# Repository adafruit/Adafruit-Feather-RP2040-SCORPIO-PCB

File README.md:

## Adafruit Feather RP2040 SCORPIO 8 Channel NeoPixel Driver PCB

<a href="http://www.adafruit.com/products/5650"><br/>
Click here to purchase one from the Adafruit shop</a>

PCB files for the Adafruit Feather RP2040 SCORPIO 8 Channel NeoPixel Driver. 

Format is EagleCAD schematic and board layout
* https://www.adafruit.com/product/5650

### Description

If there is one thing Adafruit is known for, its mega-blinky-fun-rainbow-LEDs. We just love sticking NeoPixels anywhere and everywhere. When we saw the new 'PIO' peripheral on the RP2040 from Raspberry Pi, we just knew it would be perfect for driving large quantities of NeoPixels. So we created this board, the Adafruit Feather RP2040 SCORPIO, designed specifically for NeoPixel (WS2812) driving but also good for various other PIO-based projects that want to take advantage of the Feather pinout with 8 separate consecutive outputs (or inputs).

The RP2040 PIO state machine is perfect for LED driving: it can generate perfect waveforms, with up to 8 outputs concurrently, all through DMA. That means that you don't need to use any processor time to bit-bang-out the LED data. Just set up the buffer and tell the PIO peripheral to 'make it so' and it will shove that data to the 8 outputs without delay while your code can continue to read buttons, play music, run CircuitPython - whatever you like!

The SCORPIO has a clever pinout, where all the standard Feather pins are the same as the GPIO pins, plus the standard I2C, SPI and UART lines - and theres still enough pins left over to have 8 consecutive pins for PIO usage on GPIO16 through GPIO23 inclusive.

To make NeoPixel usage glitch-free there is a 3V->5V level shifter so that the output logic is 5V. If you happen to want 3V signals, you can adjust the shifter voltage with a jumper on the bottom. It's also possible to flip the direction of the level shifter to make the 8 I/O pins inputs - say for making a logic analyzer - with a directional jumper selection also on the bottom of the PCB.

The RP2040 SCORPIO also has a ton of RAM, 264KB, making it trivial to buffer huge numbers of NeoPixels…several thousand if needed. In fact there's so much RAM you can even dither the pixels to for finer brightness control, for better-looking LEDs at low brightness or for gamma correction.

### License

Adafruit invests time and resources providing this open source design, please support Adafruit and open-source hardware by purchasing products from [Adafruit](https://www.adafruit.com)!

Designed by Limor Fried/Ladyada for Adafruit Industries.

Creative Commons Attribution/Share-Alike, all text above must be included in any redistribution. 
See license.txt for additional details.

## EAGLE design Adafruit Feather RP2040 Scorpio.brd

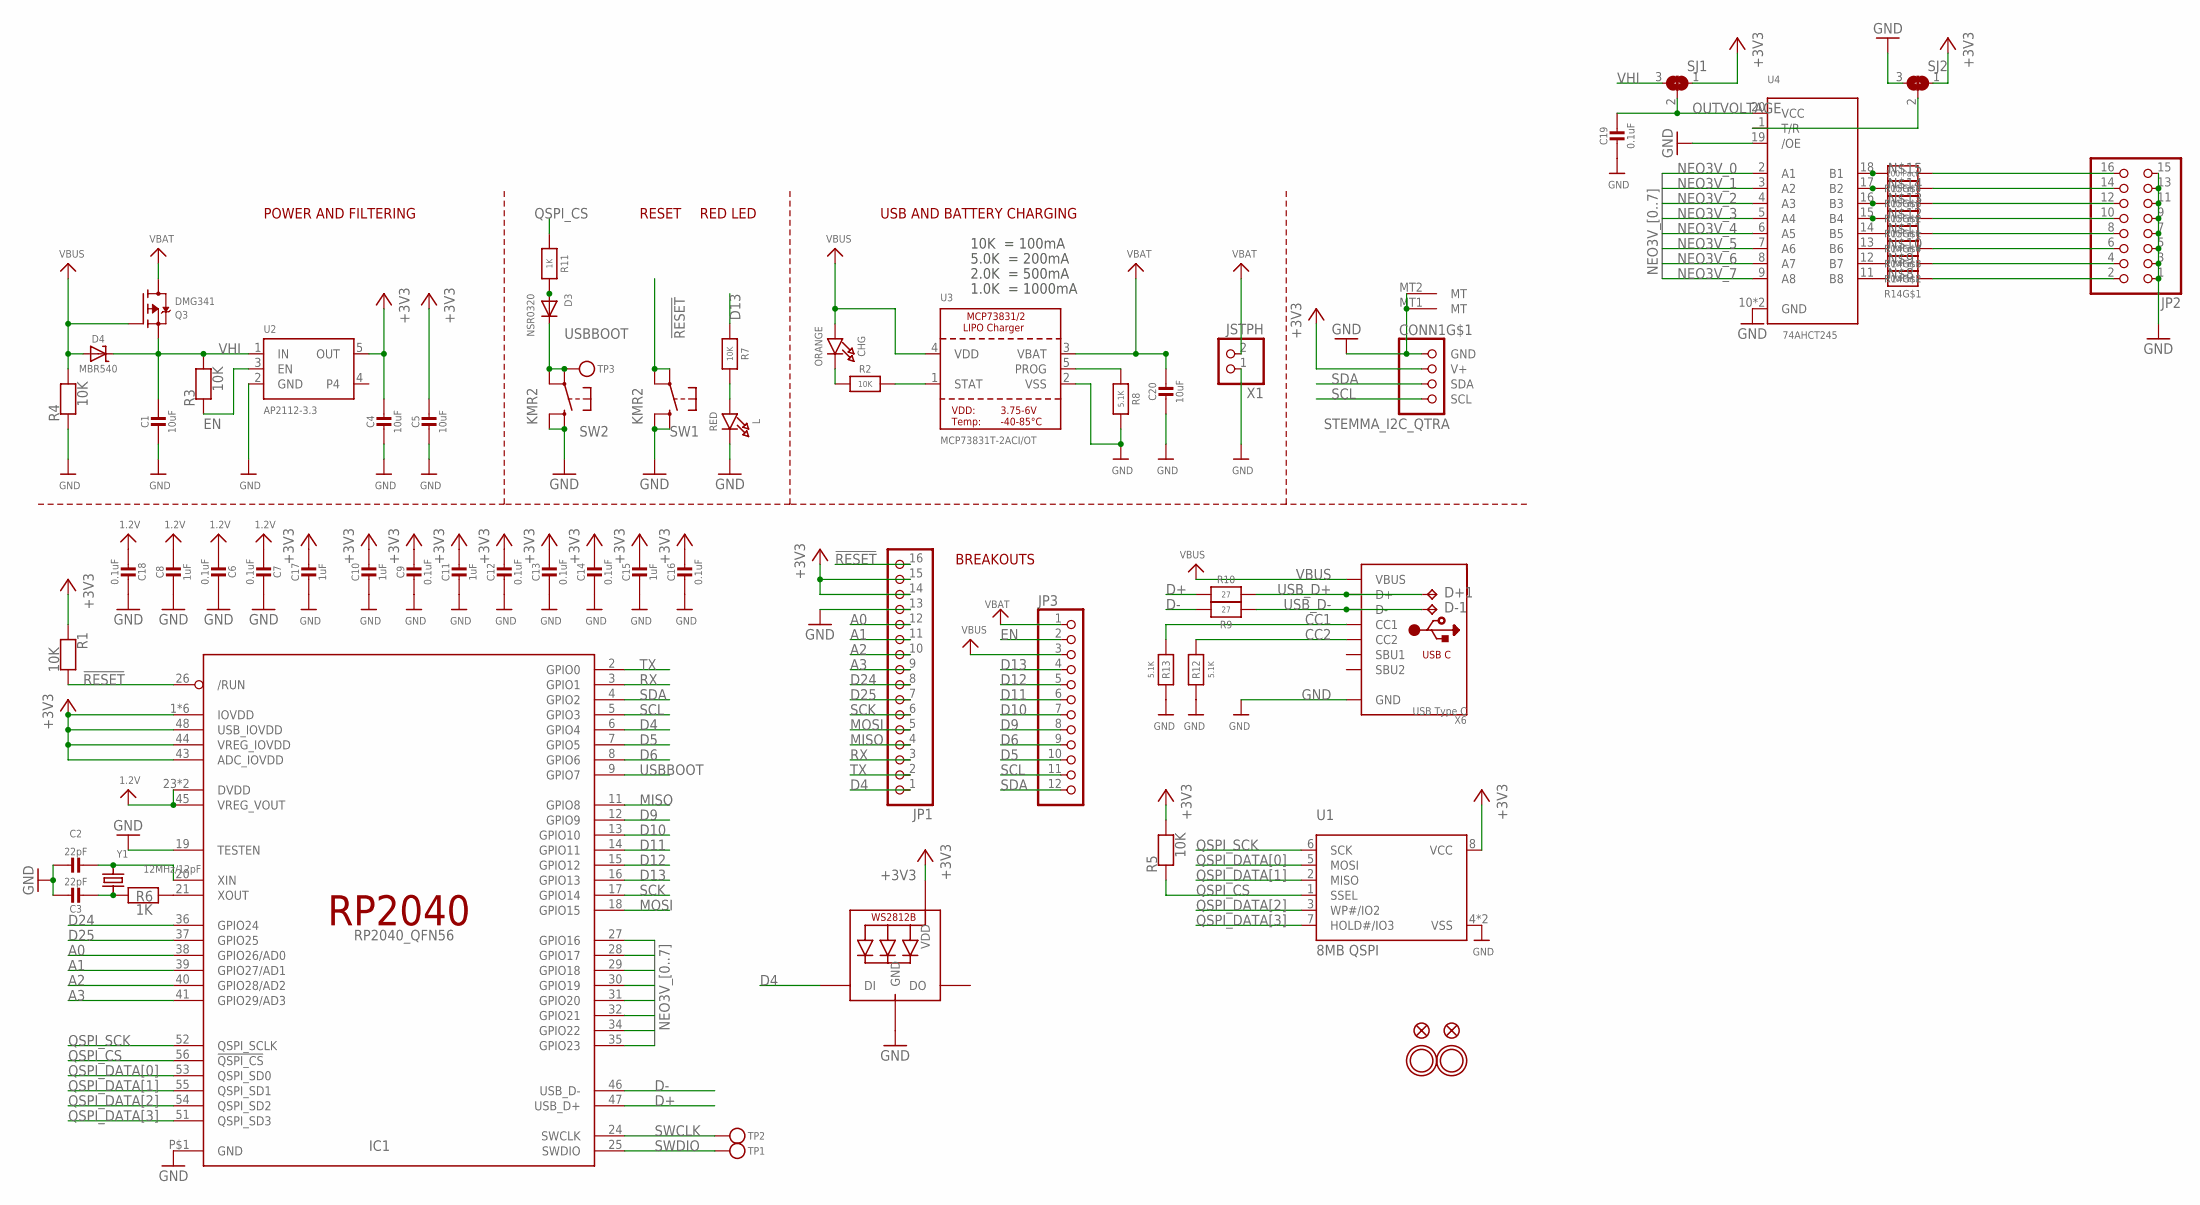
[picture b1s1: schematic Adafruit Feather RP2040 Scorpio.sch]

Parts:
C1, C4, C5, C20: 10uF; 0805-NO
C2, C3: 22pF; _0402NO
C6, C7, C9, C12, C13, C14, C16, C18, C19: 0.1uF; _0402NO
C8, C10, C11, C15, C17: 1uF; 0603-NO
CHG: ORANGE; CHIPLED_0603_NOOUTLINE
CONN1: STEMMA_I2C_QTRA; JST_SH4_RA
D3: NSR0320; SOD-323F
D4: MBR540; SOD-123
D+1: TPB1,27; B1,27
D-1: TPB1,27; B1,27
IC1: RP2040_QFN56; QFN56_7MM_REDUCEDEPAD
JP1: HEADER-1X16ROUND; 1X16_ROUND
JP2: HEADER-2X8; 2X08
JP3: HEADER-1X12; 1X12_ROUND
L: RED; CHIPLED_0603_NOOUTLINE
LED1: WS2812B_SK6805_1515; SK6805_1515
Q3: DMG341; SOT23-R
R1, R2, R3, R4, R5, R7: 10K; 0603-NO
R6, R11: 1K; 0603-NO
R8, R12, R13: 5.1K; 0603-NO
R9, R10: 27; 0603-NO
R14, R15: 100 Pack; RESPACK_4X0402
SJ1, SJ2: SOLDERJUMPER_2WAY; SOLDERJUMPER_2WAY_OPEN_NOPASTE
SW1, SW2: KMR2; BTN_KMR2_4.6X2.8
TP1, TP2, TP3: TESTPOINTROUND1.5MMNO; TESTPOINT_ROUND_1.5MM_NO
U1: 8MB QSPI; USON8_4X4
U2: AP2112-3.3; SOT23-5; JLC_ROTATION 0
U3: MCP73831T-2ACI/OT; SOT23-5
U4: 74AHCT245; 20-DHVQFN
U$31, U$32: MOUNTINGHOLE2.5; MOUNTINGHOLE_2.5_PLATED
U$34, U$35: FIDUCIAL_1MM
X1: JSTPH; JSTPH2_BATT
X6: USB Type C; USB_C_CUSB31-CFM2AX-01-X
Y1: 12MHz/12pF; CRYSTAL_2.5X2

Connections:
1.2V: C6.2, C7.2, C8.1, C18.2, IC1.23 (DVDD), IC1.45 (VREG_VOUT), IC1.50 (DVDD)
!RESET: IC1.26 (/RUN), JP1.16, R1.2, SW1.A, SW1.A' (P1)
+3V3: C4.1, C5.1, C9.1, C10.1, C11.1, C12.1, C13.1, C14.1, C15.1, C16.1, C17.1, CONN1.2 (V+), IC1.1 (IOVDD), IC1.10 (IOVDD), IC1.22 (IOVDD), IC1.33 (IOVDD), IC1.42 (IOVDD), IC1.43 (ADC_IOVDD), IC1.44 (VREG_IOVDD), IC1.48 (USB_IOVDD), IC1.49 (IOVDD), JP1.14, JP1.15, LED1.2 (VDD), R1.1, R5.2, SJ1.1, SJ2.1, U1.8 (VCC), U2.5 (OUT)
A0: IC1.38 (GPIO26/AD0), JP1.12
A1: IC1.39 (GPIO27/AD1), JP1.11
A2: IC1.40 (GPIO28/AD2), JP1.10
A3: IC1.41 (GPIO29/AD3), JP1.9
CC1: R13.2, X6.A5 (CC1)
CC2: R12.2, X6.B5 (CC2)
D4: IC1.6 (GPIO4), JP1.1, LED1.1 (DI)
D5: IC1.7 (GPIO5), JP3.10
D6: IC1.8 (GPIO6), JP3.9
D9: IC1.12 (GPIO9), JP3.8
D10: IC1.13 (GPIO10), JP3.7
D11: IC1.14 (GPIO11), JP3.6
D12: IC1.15 (GPIO12), JP3.5
D13: IC1.16 (GPIO13), JP3.4, R7.1
D24: IC1.36 (GPIO24), JP1.8
D25: IC1.37 (GPIO25), JP1.7
D+: IC1.47 (USB_D+), R10.2
D-: IC1.46 (USB_D-), R9.2
EN: JP3.2, R3.1, U2.3 (EN)
GND: C1.2, C2.1, C3.1, C4.2, C5.2, C6.1, C7.1, C8.2, C9.2, C10.2, C11.2, C12.2, C13.2, C14.2, C15.2, C16.2, C17.2, C18.1, C19.2, C20.2, CONN1.1 (GND), CONN1.MT1 (MT), CONN1.MT2 (MT), IC1.19 (TESTEN), IC1.P$1 (GND), JP1.13, JP2.1, JP2.3, JP2.5, JP2.7, JP2.9, JP2.11, JP2.13, JP2.15, L.C, LED1.4 (GND), R4.1, R8.2, R12.1, R13.1, SJ2.3, SW1.B (S), SW1.B' (S1), SW2.B (S), SW2.B' (S1), U1.4 (VSS), U1.PAD (VSS), U2.2 (GND), U3.2 (VSS), U4.10 (GND), U4.19 (/OE), U4.21 (GND), X1.1, X6.A1B12 (GND), X6.B1A12 (GND)
MISO: IC1.11 (GPIO8), JP1.4
MOSI: IC1.18 (GPIO15), JP1.5
unnamed: CHG.C, R2.1
unnamed: L.A, R7.2
unnamed: R2.2, U3.1 (STAT)
unnamed: R8.1, U3.5 (PROG)
unnamed: C2.2, IC1.20 (XIN), Y1.3 (2)
unnamed: C3.2, R6.1, Y1.1
unnamed: IC1.21 (XOUT), R6.2
unnamed: R14.8 (2), U4.11 (B8)
unnamed: R14.7 (2), U4.12 (B7)
unnamed: R14.6 (2), U4.13 (B6)
unnamed: R14.5 (2), U4.14 (B5)
unnamed: R15.8 (2), U4.15 (B4)
unnamed: R15.7 (2), U4.16 (B3)
unnamed: R15.6 (2), U4.17 (B2)
unnamed: R15.5 (2), U4.18 (B1)
unnamed: D3.A, R11.2
unnamed: SJ2.2, U4.1 (T/R)
NEO0: JP2.16, R15.4 (1)
NEO1: JP2.14, R15.3 (1)
NEO2: JP2.12, R15.2 (1)
NEO3: JP2.10, R15.1
NEO3V_0: IC1.27 (GPIO16), U4.2 (A1)
NEO3V_1: IC1.28 (GPIO17), U4.3 (A2)
NEO3V_2: IC1.29 (GPIO18), U4.4 (A3)
NEO3V_3: IC1.30 (GPIO19), U4.5 (A4)
NEO3V_4: IC1.31 (GPIO20), U4.6 (A5)
NEO3V_5: IC1.32 (GPIO21), U4.7 (A6)
NEO3V_6: IC1.34 (GPIO22), U4.8 (A7)
NEO3V_7: IC1.35 (GPIO23), U4.9 (A8)
NEO4: JP2.8, R14.4 (1)
NEO5: JP2.6, R14.3 (1)
NEO6: JP2.4, R14.2 (1)
NEO7: JP2.2, R14.1
OUTVOLTAGE: C19.1, SJ1.2, U4.20 (VCC)
QSPI_CS: IC1.56 (!QSPI_CS), R5.1, R11.1, U1.1 (SSEL)
QSPI_DATA[0]: IC1.53 (QSPI_SD0), U1.5 (MOSI)
QSPI_DATA[1]: IC1.55 (QSPI_SD1), U1.2 (MISO)
QSPI_DATA[2]: IC1.54 (QSPI_SD2), U1.3 (WP#/IO2)
QSPI_DATA[3]: IC1.51 (QSPI_SD3), U1.7 (HOLD#/IO3)
QSPI_SCK: IC1.52 (QSPI_SCLK), U1.6 (SCK)
RX: IC1.3 (GPIO1), JP1.3
SCK: IC1.17 (GPIO14), JP1.6
SCL: CONN1.4 (SCL), IC1.5 (GPIO3), JP3.11
SDA: CONN1.3 (SDA), IC1.4 (GPIO2), JP3.12
SWCLK: IC1.24 (SWCLK), TP2.P$1
SWDIO: IC1.25 (SWDIO), TP1.P$1
TX: IC1.2 (GPIO0), JP1.2
USBBOOT: D3.C, IC1.9 (GPIO7), SW2.A, SW2.A' (P1), TP3.P$1
USB_D+: D+1.TP, R10.1, X6.A6 (D+), X6.B6 (D+)
USB_D-: D-1.TP, R9.1, X6.A7 (D-), X6.B7 (D-)
VBAT: C20.1, JP3.1, Q3.3 (D), U3.3 (VBAT), X1.2
VBUS: CHG.A, D4.A, JP3.3, Q3.1 (G), R4.2, U3.4 (VDD), X6.A4B9 (VBUS), X6.B4A9 (VBUS)
VHI: C1.1, D4.C, Q3.2 (S), R3.2, SJ1.3, U2.1 (IN)

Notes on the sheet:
POWER AND FILTERING
RESET
10K = 100mA
5.0K = 200mA
2.0K = 500mA
1.0K = 1000mA
USB AND BATTERY CHARGING
BREAKOUTS
RED LED

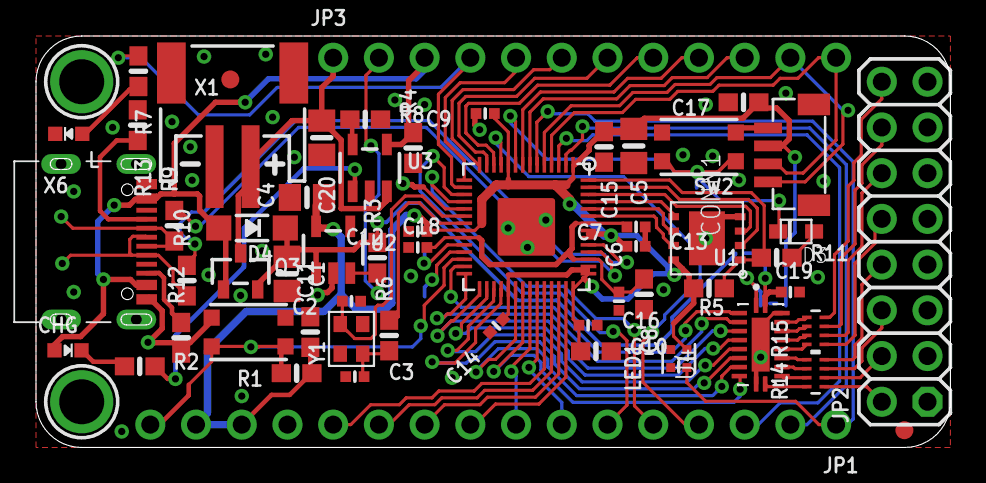
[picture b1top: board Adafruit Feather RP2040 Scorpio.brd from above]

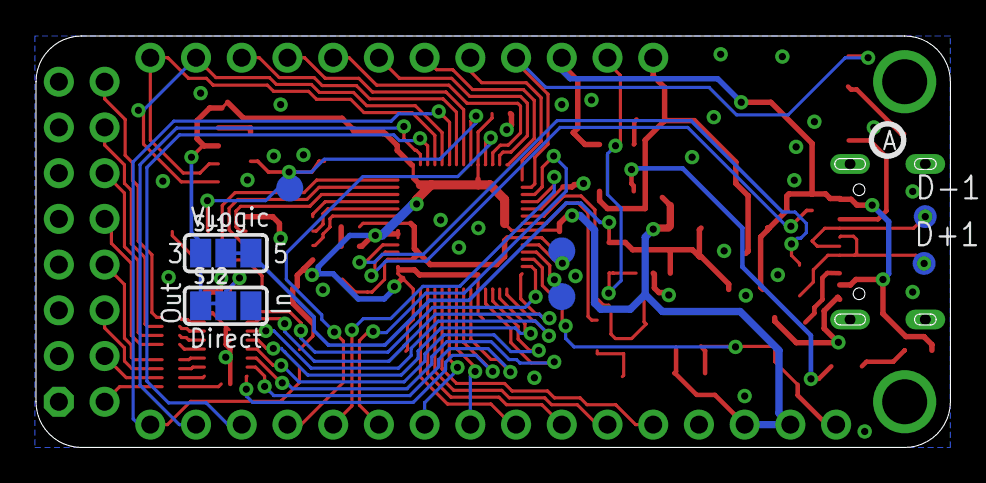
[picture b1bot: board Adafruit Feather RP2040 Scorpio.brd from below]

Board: 2 copper layers, 50.8 x 22.9 mm, 69 parts (9 on the bottom side), 78 nets.

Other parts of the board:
U$12: SCORPIO_TOP
U$13: PCBFEAT-REV-040
U$28: SCORPIO_BOT

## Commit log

2023-02-07 Initial commit - Added PCB files

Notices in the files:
parts and their libraries:
microbuilder: This work is placed in the public domain, and may be freely used for commercial and non-commercial work with the following conditions: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
